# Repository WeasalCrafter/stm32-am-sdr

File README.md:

<!-- kicad_template/README.md -->

# STM32-Based SDR Rated for 0.5MHz to 50MHz

This repository contains all KiCad files relating to my STM-32 SDR project.

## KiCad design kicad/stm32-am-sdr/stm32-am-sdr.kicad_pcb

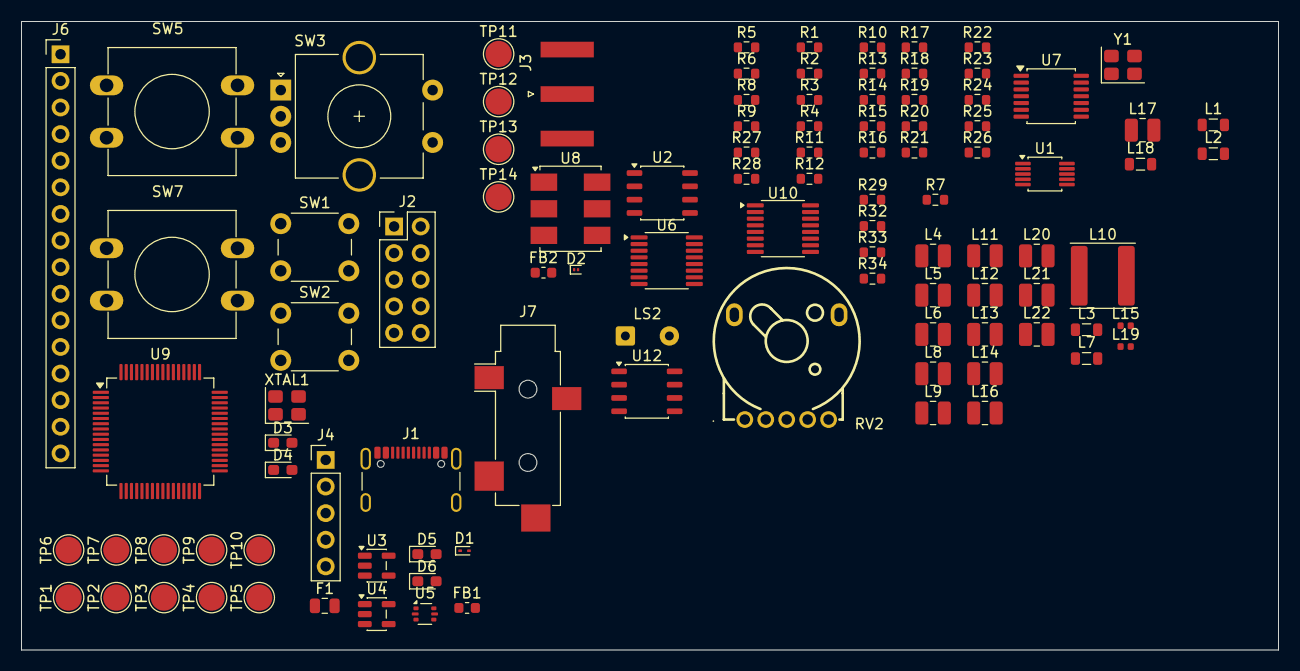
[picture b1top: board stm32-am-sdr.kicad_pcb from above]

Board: 4 copper layers, 120.0 x 60.0 mm, 103 parts (0 on the bottom side), 95 nets, no tracks yet.

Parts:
D1: DF2S6.8FS,L3M; D_SOD-923
D2: ESD131-B1-W0201; Infineon_SG-WLL-2-3_0.58x0.28_P0.36mm
D3, D4, D5, D6: LED; LED_0603_1608Metric_Pad1.05x0.95mm_HandSolder
F1: Polyfuse_Small; Fuse_0805_2012Metric
FB1, FB2: FerriteBead_Small; L_0603_1608Metric
J1: USB_C_Receptacle_USB2.0_14P; USB_C_Receptacle_GCT_USB4105-xx-A_16P_TopMnt_Horizontal
J2: Conn_ARM_JTAG_SWD_10; PinHeader_2x05_P2.54mm_Vertical
J3: Conn_Coaxial_Small; SMA_Amphenol_132289_EdgeMount
J4: Conn_01x05; PinHeader_1x05_P2.54mm_Vertical
J6: Conn_01x16; PinHeader_1x16_P2.54mm_Vertical
J7: AudioJack3_SwitchT; Jack_3.5mm_CUI_SJ-3524-SMT_Horizontal
L1, L2: 360nH; L_0805_2012Metric
L3, L7: 18uH; L_0805_2012Metric
L4, L6: 10uH; L_1008_2520Metric
L5, L9, L11: 5.6uH; L_1008_2520Metric
L8, L12: 3.9uH; L_1008_2520Metric
L10: 1.3uH; L_Chilisin_BWVS00606028
L13, L21: 1.8uH; L_1008_2520Metric
L14, L22: 820nH; L_1008_2520Metric
L15, L19: 2uH; L_0402_1005Metric
L16, L20: 680nH; L_1008_2520Metric
L17: 560nH; L_1008_2520Metric
L18: 240nH; L_0805_2012Metric
LS2: Speaker; SolderWire-0.25sqmm_1x02_P4.2mm_D0.65mm_OD1.7mm
R1, R2, R8, R9: 2.2K; R_0603_1608Metric
R3, R4, R10, R24, R26: 10K; R_0603_1608Metric
R5, R6: 5.1K; R_0603_1608Metric
R7: 22; R_0603_1608Metric
R11, R12, R27, R28, R34: 150; R_0603_1608Metric
R13, R14, R15, R16, R20, R21, R22: 100; R_0603_1608Metric
R17, R19: 4.99k; R_0603_1608Metric
R18: 0; R_0603_1608Metric
R23, R25, R29: 1K; R_0603_1608Metric
R32, R33: 100K; R_0603_1608Metric
RV2: 10K; RES-TH_RK10J12E0A0A
SW1: RESET; SW_PUSH_6mm_H4.3mm
SW2: BOOT; SW_PUSH_6mm_H4.3mm
SW3: RotaryEncoder_Switch; RotaryEncoder_Alps_EC11E-Switch_Vertical_H20mm_CircularMoun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
SW5, SW7: SW_Push; SW_PUSH-12mm
TP1, TP2, TP3, TP4, TP5, TP6, TP7, TP8, TP9, TP10, TP11, TP12, TP13, TP14: TestPoint; TestPoint_Pad_D2.5mm
U1: Si5351A-B-GT; MSOP-10_3x3mm_P0.5mm
U2: LT6231CS8; JEITA_SOIC-8_3.9x4.9mm_P1.27mm
U3, U4: TPS7A20xxxDBV; SOT-23-5
U5: USBLC6-2P6; SOT-666
U6, U10: PI3B3253QEX-2017; QSOP-16_3.9x4.9mm_P0.635mm
U7: SN74LVC74APWR; TSSOP-14_4.4x5mm_P0.65mm
U8: ADTT4-1+; Mini-Circuits_CD636_H4.11mm
U9: STM32G431RBT6; LQFP-64_10x10mm_P0.5mm
U12: LM4875; JEITA_SOIC-8_3.9x4.9mm_P1.27mm
XTAL1: FL2400022; Crystal_SMD_3225-4Pin_3.2x2.5mm
Y1: 7M-27.000MEEQ-T; Crystal_SMD_3225-4Pin_3.2x2.5mm

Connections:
+1V65: J4.4, R8.2, R9.2, TP5.1 (1_1), U8.5 (SEC_{CT})
+3V3: J2.1 (VTref), J4.2, J6.1, R1.1, R2.2, R4.2, R27.1, SW2.1, U1.1 (VDD), U1.7 (VDDO), U3.5 (OUT), U7.1 (1~CLR), U7.4 (1~PRE), U7.10 (2~PRE), U7.13 (2~CLR), U7.14 (VCC), U9.1 (VBAT), U9.16 (VDD), U9.32 (VDD), U9.48 (VDD), U9.64 (VDD)
+3V3A: FB1.2, J4.3, R8.1, R22.2, R28.1, TP4.1 (1_1), U2.8 (V+), U6.16 (VCC), U9.28 (VREF+), U9.29 (VDDA)
/AUDIO_SIG: R29.1, U9.19 (PA5)
/Audio/AUD_SW: J7.TN, R32.2, R33.1
/Bandpass Filter Selector/BPF_In: L2.2, R18.1, U10.7 (YA)
/Bandpass Filter Selector/BPF_Out: R18.2, U10.9 (YB)
/Bandpass Filter Selector/IA0: L3.1, U10.6 (IA0)
/Bandpass Filter Selector/IA1: L8.1, U10.5 (IA1)
/Bandpass Filter Selector/IA2: L13.1, U10.4 (IA2)
/Bandpass Filter Selector/IA3: L14.1, U10.3 (IA3)
/Bandpass Filter Selector/IB0: L6.2, L7.1, U10.10 (IB0)
/Bandpass Filter Selector/IB1: L11.2, L12.1, U10.11 (IB1)
/Bandpass Filter Selector/IB2: L19.2, L21.1, U10.12 (IB2)
/Bandpass Filter Selector/IB3: L20.2, L22.1, U10.13 (IB3)
/Bandpass Filter Selector/S0: R23.2, R24.1, U10.14 (S0)
/Bandpass Filter Selector/S1: R25.2, R26.1, U10.2 (S1)
/CLK_I: TP2.1 (1_1), U6.14 (S0), U7.5 (1Q), U7.12 (2D)
/CLK_Q: TP3.1 (1_1), U6.2 (S1), U7.9 (2Q)
/I_OUT: R20.2, TP6.1 (1_1), U9.17 (PA3)
/MCU_D+: U5.4 (I/O2), U9.46 (PA12)
/MCU_D-: U5.6 (I/O1), U9.45 (PA11)
/Power and USB/CC1: J1.A5 (CC1), R5.2
/Power and USB/CC2: J1.B5 (CC2), R6.2
/Power and USB/D+: J1.A6 (D+), J1.B6 (D+), U5.3 (I/O2)
/Power and USB/D-: J1.A7 (D-), J1.B7 (D-), U5.1 (I/O1)
/Q_OUT: R21.2, TP7.1 (1_1), U9.18 (PA4)
/RF Input and Tayloe Detector/0A: R13.1, TP11.1 (1_1), U6.6 (IA0), U6.13 (IB3)
/RF Input and Tayloe Detector/0B: R14.1, TP13.1 (1_1), U6.3 (IA3), U6.10 (IB0)
/RF Input and Tayloe Detector/270A: R16.1, TP14.1 (1_1), U6.4 (IA2), U6.11 (IB1)
/RF Input and Tayloe Detector/270B: R15.1, TP12.1 (1_1), U6.5 (IA1), U6.12 (IB2)
/RF Input and Tayloe Detector/RF: U6.7 (YA), U8.6 (SEC)
/RF Input and Tayloe Detector/~RF: U6.9 (YB), U8.4 (SEC_{DOT})
/Reference Clock/1D: U7.2 (1D), U7.8 (2~Q)
/Reference Clock/CLK_LO: R7.2, U7.3 (1CLK), U7.11 (2CLK)
/Reference Clock/XA: U1.2 (XA), Y1.3
/Reference Clock/XB: U1.3 (XB), Y1.1
/SCL: J6.3, R1.2, TP9.1 (1_1), U1.4 (SCL), U9.51 (PA15)
/SDA: J6.4, R2.1, TP8.1 (1_1), U1.5 (SDA), U9.60 (PB7)
/STM32 Microcontroller/BLUE_LED: R12.1, U9.62 (PB9)
/STM32 Microcontroller/BOOT0: R3.1, SW2.2, U9.61 (PB8)
/STM32 Microcontroller/NRST: J2.10 (~RESET), R4.1, SW1.2, U9.7 (PG10)
/STM32 Microcontroller/OSC_IN: U9.5 (PF0), XTAL1.1
/STM32 Microcontroller/OSC_OUT: U9.6 (PF1), XTAL1.3
/STM32 Microcontroller/PA0: J6.15, U9.12 (PA0)
/STM32 Microcontroller/PA1: J6.16, U9.13 (PA1)
/STM32 Microcontroller/PA8: J6.11, U9.42 (PA8)
/STM32 Microcontroller/PB10: J6.12, U9.30 (PB10)
/STM32 Microcontroller/PB11: J6.13, U9.33 (PB11)
/STM32 Microcontroller/PB12: J6.5, U9.34 (PB12)
/STM32 Microcontroller/PB13: J6.6, U9.35 (PB13)
/STM32 Microcontroller/PB14: J6.7, U9.36 (PB14)
/STM32 Microcontroller/PB15: J6.8, U9.37 (PB15)
/STM32 Microcontroller/PC4: J6.14, U9.22 (PC4)
/STM32 Microcontroller/PC6: SW3.A, U9.38 (PC6)
/STM32 Microcontroller/PC7: SW3.B, U9.39 (PC7)
/STM32 Microcontroller/PC8: SW3.S1, U9.40 (PC8)
/STM32 Microcontroller/PC10: J6.9, U9.52 (PC10)
/STM32 Microcontroller/PC11: J6.10, U9.53 (PC11)
/STM32 Microcontroller/PC12: SW7.1, U9.54 (PC12)
/STM32 Microcontroller/PC13: SW5.1, U9.2 (PC13)
/STM32 Microcontroller/RED_LED: R11.1, U9.58 (PB5)
/STM32 Microcontroller/SWCLK: J2.4 (SWCLK/TCK), U9.50 (PA14)
/STM32 Microcontroller/SWDIO: J2.2 (SWDIO/TMS), U9.49 (PA13)
/STM32 Microcontroller/SWO: J2.6 (SWO/TDO), U9.56 (PB3)
/Select_BPF_0: R23.1, U9.24 (PB0)
/Select_BPF_1: R25.1, U9.25 (PB1)
GND: D1.2 (A), D3.1 (K), D4.1 (K), D5.1 (K), D6.1 (K), FB2.2, J1.A1 (GND), J1.A12 (GND), J1.B1 (GND), J1.B12 (GND), J1.SH (SHIELD), J2.3 (GND), J2.5 (GND), J2.9 (GNDDetect), J4.5, J6.2, J7.S, R3.2, R5.1, R6.1, R9.1, R34.1, RV2.3, SW1.1, SW3.C, SW3.S2, SW5.2, SW7.2, TP1.1 (1_1), TP10.1 (1_1), U1.8 (GND), U2.4 (V-), U3.2 (GND), U4.2 (GND), U5.2 (GND), U6.1 (~EA), U6.8 (GND), U6.15 (~EB), U7.7 (GND), U9.15 (VSS), U9.27 (VSSA), U9.31 (VSS), U9.47 (VSS), U9.63 (VSS), U12.6 (GND), XTAL1.2, XTAL1.4, Y1.2, Y1.4
unnamed: L1.2, L2.1
unnamed: L4.2, L5.1
unnamed: L9.2, L10.1
unnamed: L15.2, L17.1
unnamed: L16.2, L18.1
unnamed: R17.2, R20.1, U2.1
unnamed: R19.2, R21.1, U2.7
unnamed: J7.R, J7.T, R34.2
unnamed: D2.2 (A2), J3.1 (In), L1.1, R10.1
unnamed: D3.2 (A), R11.2
unnamed: D4.2 (A), R12.2
unnamed: D5.2 (A), R27.2
unnamed: D6.2 (A), R28.2
unnamed: R7.1, U1.10 (CLK0)
unnamed: R13.2, U2.3 (+)
unnamed: R14.2, R17.1, U2.2 (-)
unnamed: R15.2, U2.5 (+)
unnamed: R16.2, R19.1, U2.6 (-)
unnamed: FB1.1, U4.5 (OUT)
unnamed: R22.1, U10.16 (VCC)
unnamed: RV2.2, U12.4 (DC_Vol/~SD)
unnamed: R33.2, U12.3 (HP_Sense)
unnamed: LS2.2, U12.5 (Vo1)
unnamed: LS2.1, U12.8 (Vo2)
RF-GND: D2.1 (A1), FB2.1, J3.2 (Ext), L3.2, L5.2, L7.2, L8.2, L10.2, L12.2, L13.2, L14.2, L17.2, L18.2, L21.2, L22.2, R10.2, R24.2, R26.2, U8.1 (PRI), U10.1 (~EA), U10.8 (GND), U10.15 (~EB)
VBUS: F1.1, J1.A4 (VBUS), J1.A9 (VBUS), J1.B4 (VBUS), J1.B9 (VBUS), U5.5 (VBUS)
VIN: D1.1 (K), F1.2, J4.1, R32.1, RV2.1, U3.1 (IN), U3.3 (EN), U4.1 (IN), U4.3 (EN), U12.1 (VDD)
